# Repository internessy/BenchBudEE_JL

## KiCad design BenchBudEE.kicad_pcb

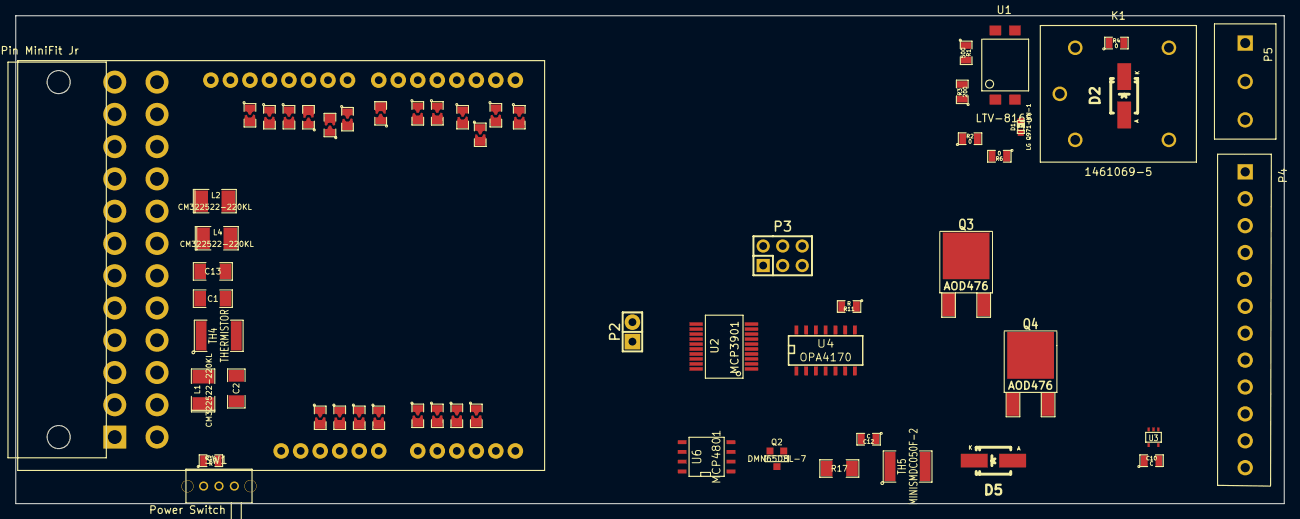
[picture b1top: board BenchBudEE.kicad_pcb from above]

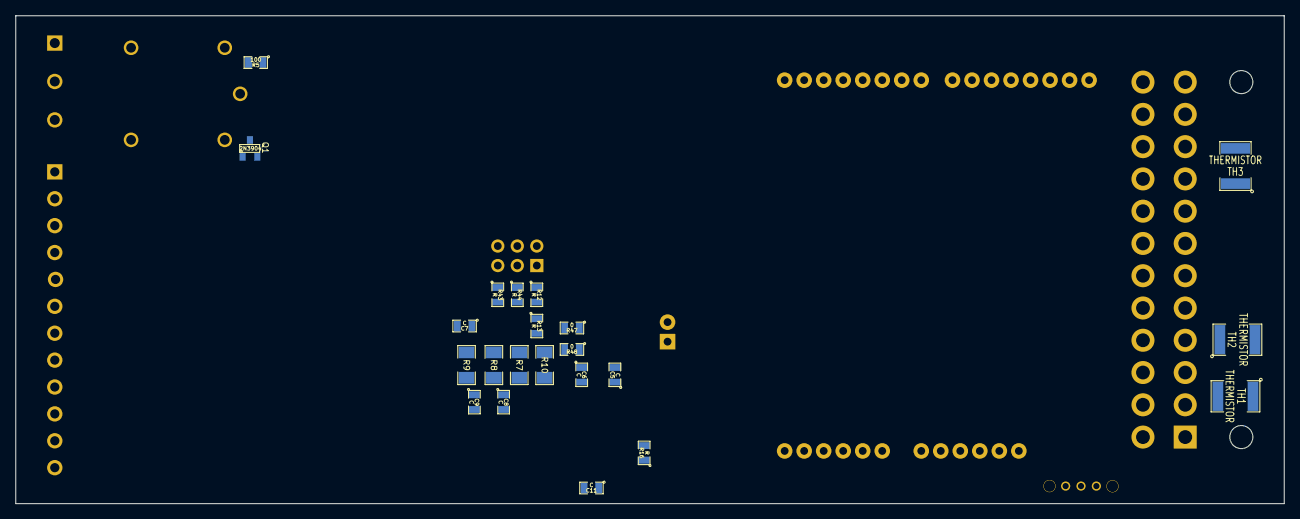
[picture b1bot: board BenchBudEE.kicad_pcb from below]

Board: 4 copper layers, 165.1 x 63.5 mm, 80 parts (22 on the bottom side), 81 nets, no tracks yet.

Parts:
ARD1: ARDUINO_PINS; arduino
C1, C2, C13: C; SM1206
C5, C6, C7, C8, C9, C10, C11, C12: C; SM0805
D1: LG Q971-KN-1; LED-0603
D2, D5: B130-13-F; Diode-SMA_Handsoldering
K1: 1461069-5; TE-SPDT
L1, L2, L4: CM322522-220KL; SM1210L
P1: 24 Pin MiniFit Jr; ATX_Header
P2: CONN_2; Pin_Header_Straight_1x02
P3: CONN_3X2; Pin_Header_Straight_2x03
P4: 12 Pin Terminal Block; 12pinTB
P5: 3-Pin TB; 3pinTB
Q1: 2N3904; SOT23
Q2: DMN65D8L-7; SOT23GDS
Q3, Q4: AOD476; DPAKGDS
R1: 500; SM0805
R2, R4, R6, R47, R48: 0; SM0805
R3: 200; SM0805
R5: 100; SM0805
R7, R8, R9, R10, R17: R; SM1206
R11, R12, R13, R14, R16, R43, R44: R; SM0805
R28, R29, R30, R31, R32, R33, R34, R35, R36, R37, R38, R39, R40, R41, R45, R46, R49, R50, R51, R52, R53: R; SM0805_BLOB_BRIDGE
SW1: Power Switch; BB_powerSwitch
TH1, TH2, TH3, TH4: THERMISTOR; SM1812
TH5: MINISMDC050F-2; SM1812
U1: LTV-816S; 4-SMD
U2: MCP3901; SSOP-20_5.3mm
U3: LMT84; SOT353
U4: OPA4170; SO14E
U6: MCP4801; SO8N

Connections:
+3.3V: P4.1, R14.2, TH1.2
+5V: C6.1, C10.1, C11.2, C13.1, L4.2, P4.2, R49.1, TH2.2, U2.3, U3.4, U6.1
+12C: C12.1, P1.10, TH3.1, TH5.1
+12P: L2.1, R28.1, TH3.2
+12V: C1.1, C9.1, R2.1, R4.1, U4.4
-12P: L1.1, TH4.2
-12V: C2.2, C7.1, L1.2, U4.11
/Arduino/CURR_MEAS: Q3.D, Q4.S, R17.1, R31.1, U4.6
/Arduino/FAN_MODE: Q3.G, R41.2
/Arduino/FAN_PWM: Q2.G, R37.2
/Arduino/MISO: R35.2, U2.19
/Arduino/MOSI: R36.2, U2.20, U6.4
/Arduino/RELAY+: R33.2, U1.1
/Arduino/SCLK: R34.2, U2.18, U6.3
/Arduino/~ADC_CS: R39.2, U2.17
/Arduino/~DR: R46.2, U2.14
/Arduino/~LDAC: R52.2, U6.5
/Arduino/~RESET: R45.2, U2.1
/Arduino/~SHDN: R53.2, U6.6
/Fan/CS_N: R40.2, U6.2
/Fan/FAN_OUT+: D5.2, TH5.2
/Fan/FAN_OUT-: D5.1, Q4.D
/Relay/RELAY_COM: K1.1, P5.2
/Relay/RELAY_NC: K1.4, P5.3
/Relay/RELAY_NO: K1.3, P5.1
/ThermoCouple/CH0+: C8.1, R7.1, U2.4, U4.1
/ThermoCouple/CH0-: R48.1, U2.5
/ThermoCouple/CH1+: U2.7, U3.3
/ThermoCouple/CH1-: R47.1, U2.6
/ThermoCouple/TC IN +: P4.11, U4.10
/ThermoCouple/TC IN -: P4.12, U4.12
AGND: C5.1, C6.2, C7.2, C8.2, C9.2, C10.2, C11.1, C12.2, Q2.S, Q3.S, R8.1, R17.2, R47.2, R48.2, U2.8, U2.11, U3.1, U3.2, U3.5, U6.7
GND: C1.2, C2.1, C13.2, P1.3, P1.5, P4.3, R3.2, R6.2, R50.1, R51.1, SW1.3
unnamed: ARD1.1, R49.2
unnamed: ARD1.2, R50.2
unnamed: ARD1.3, R51.2
unnamed: ARD1.4, R28.2
unnamed: ARD1.5, R29.2
unnamed: ARD1.6, R30.2
unnamed: ARD1.7, R31.2
unnamed: ARD1.8, R32.2
unnamed: ARD1.11, R41.1
unnamed: ARD1.12, R33.1
unnamed: ARD1.13, R53.1
unnamed: ARD1.14, R52.1
unnamed: ARD1.15, R46.1
unnamed: ARD1.16, R45.1
unnamed: ARD1.18, R40.1
unnamed: ARD1.19, R39.1
unnamed: ARD1.20, R38.1
unnamed: ARD1.21, R37.1
unnamed: ARD1.22, R36.1
unnamed: ARD1.23, R35.1
unnamed: ARD1.24, R34.1
unnamed: C5.2, U2.2
unnamed: D1.1, R3.1
unnamed: D1.2, R5.1, U1.3
unnamed: D2.1, K1.5, Q1.3
unnamed: D2.2, K1.2, R4.2
unnamed: P1.2, TH1.1
unnamed: P1.4, P1.6, TH2.1
unnamed: P1.14, TH4.1
unnamed: P2.1, U2.13
unnamed: P2.2, U2.12
unnamed: P3.1, R12.1
unnamed: P3.2, P3.4, P3.6, R11.2, U4.9
unnamed: P3.3, R43.1
unnamed: P3.5, R44.1
unnamed: Q1.1, R6.1
unnamed: Q1.2, R5.2
unnamed: Q2.D, R16.2, U4.5
unnamed: Q4.G, U4.7
unnamed: R1.2, U1.2
unnamed: R2.2, U1.4
unnamed: R7.2, R9.1, U4.2
unnamed: R8.2, R10.1, U4.3
unnamed: R10.2, R13.2, U4.14
unnamed: R9.2, R11.1, U4.8
unnamed: R12.2, R13.1, R43.2, R44.2, U4.13
unnamed: R14.1, SW1.1
unnamed: R16.1, U6.8

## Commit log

2014-02-01 First Commit
    Blank Schematic and Board layout added
2014-02-01 Create Hierachical Sheets
    added first pins to TC
2014-02-01 Save Project
2014-02-01 create inputs and outputs for main modules
2014-02-03 Added Start of thermocouple circuit
2014-02-03 Added Fan control outline
2014-02-03 Added Relay module outline
2014-02-03 Added Power Module outline
2014-02-03 Added power conditioning outline
    did not add current sensing circuit
2014-02-03 Updated master sheet
2014-02-04 Added missing bit
2014-02-04 Added LED Driver Module Outline
2014-02-04 Hooked up top level schematic
2014-02-04 Fan Current module refactoring
2014-02-16 before layout
2014-02-17 Begin Associating relay Module
2014-02-18 Placed Relay Module Components
2014-02-18 Associated Thermocouple module
2014-02-18 place thermocouple components
2014-02-18 ABOUT TO REPLACE ssop20
2014-02-18 Placement of connectors
2014-02-19 Placed arduino module
2014-02-19 more changes?
2014-02-21 associated power module
2014-02-21 placed power module
